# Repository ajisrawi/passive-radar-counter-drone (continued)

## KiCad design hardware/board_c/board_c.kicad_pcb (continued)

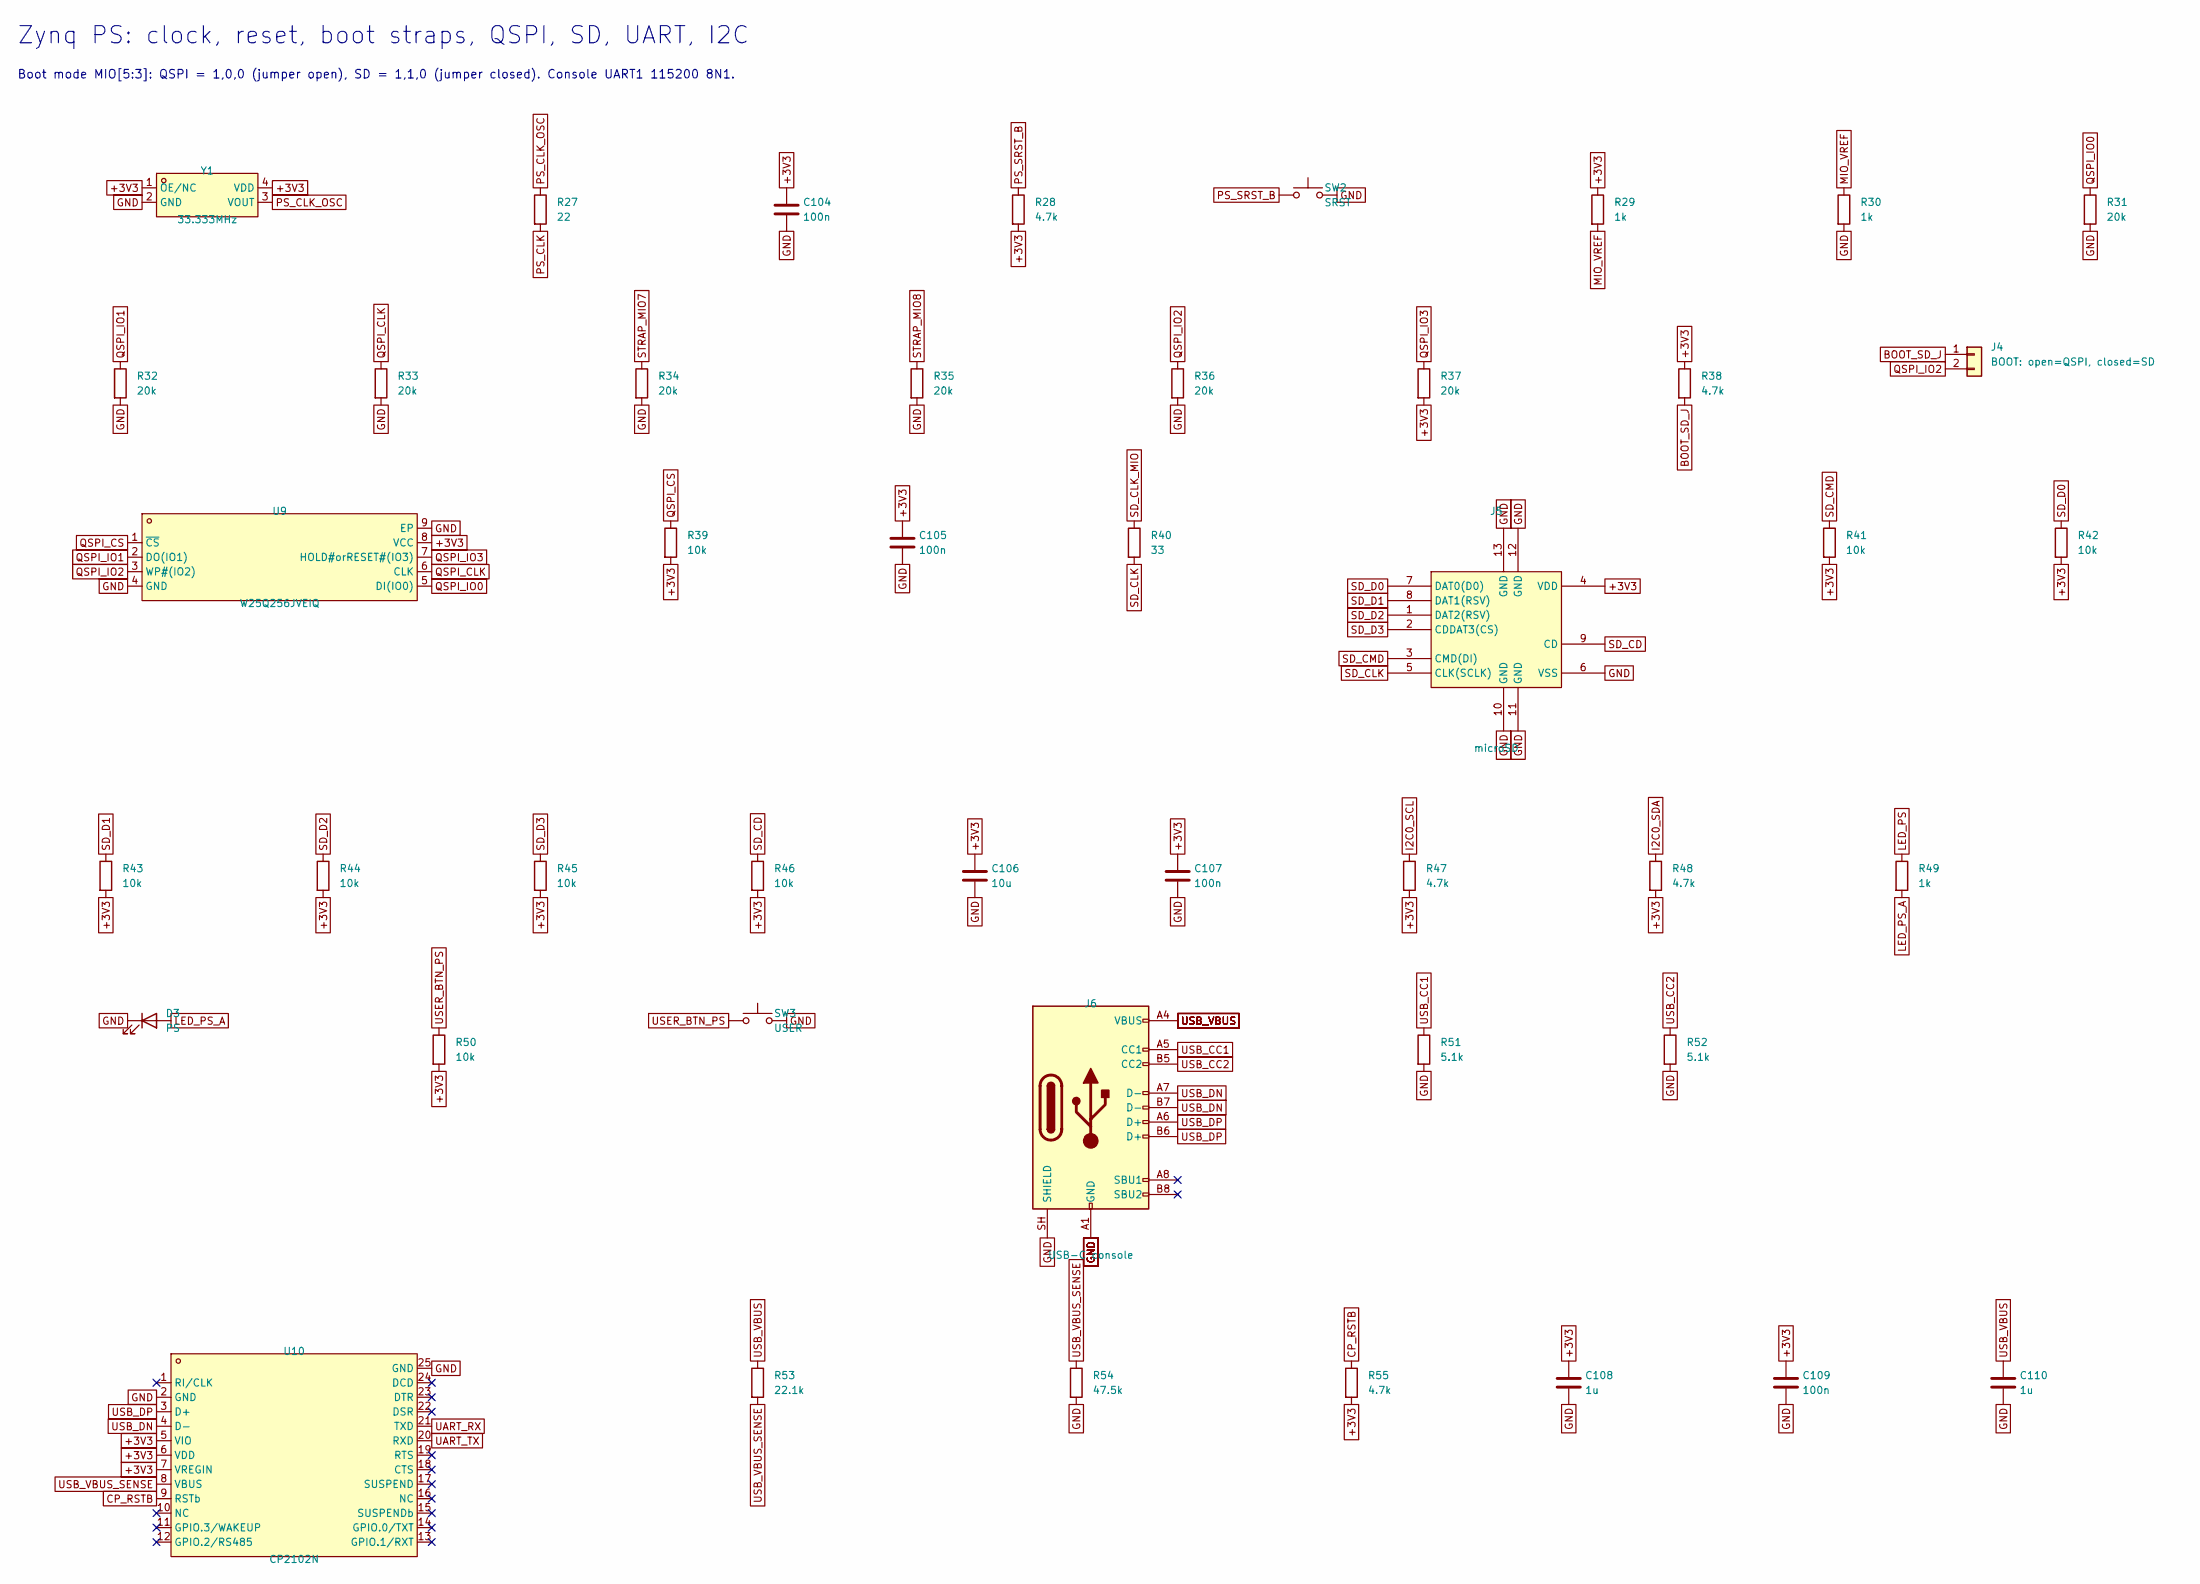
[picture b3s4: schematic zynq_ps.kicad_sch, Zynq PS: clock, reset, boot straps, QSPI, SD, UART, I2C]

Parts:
C104, C105, C107, C109: 100n; C_0402_1005Metric; LCSC C1525
C106: 10u; C_0603_1608Metric; LCSC C19702
C108, C110: 1u; C_0402_1005Metric; LCSC C52923
D3: PS; LED_0603_1608Metric
J4: BOOT: open=QSPI, closed=SD; PinHeader_1x02_P2.54mm_Vertical
J5: microSD; TF-SMD_TF-01A; MPN TF-01A; LCSC C91145
J6: USB-C console; USB_C_Receptacle_HRO_TYPE-C-31-M-12; LCSC C165948
R27: 22; R_0402_1005Metric
R28, R38, R47, R48, R55: 4.7k; R_0402_1005Metric; LCSC C25900
R29, R30, R49: 1k; R_0402_1005Metric; LCSC C11702
R31, R32, R33, R34, R35, R36, R37: 20k; R_0402_1005Metric
R39, R41, R42, R43, R44, R45, R46, R50: 10k; R_0402_1005Metric; LCSC C25744
R40: 33; R_0402_1005Metric
R51, R52: 5.1k; R_0402_1005Metric; LCSC C25905
R53: 22.1k; R_0402_1005Metric
R54: 47.5k; R_0402_1005Metric
SW2: SRST; SW_SPST_TL3342
SW3: USER; SW_SPST_TL3342
U9: W25Q256JVEIQ; WSON-8_L8.0-W6.10-P1.27-BL-EP; MPN W25Q256JVEIQ; LCSC C97522
U10: CP2102N; QFN-24_L4.0-W4.0-P0.50-TL-EP2.6; MPN CP2102N-A02-GQFN24R; LCSC C969151
Y1: 33.333MHz; OSC-SMD_4P-L5.0-W3.2-BL_OG8EL89CEI; MPN OG1EL89CEI-112YLC-33.333M; LCSC C5346412

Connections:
+3V3: C104.1, C105.1, C106.1, C107.1, C108.1, C109.1, J5.4 (VDD), R28.2, R29.1, R37.2, R38.1, R39.2, R41.2, R42.2, R43.2, R44.2, R45.2, R46.2, R47.2, R48.2, R50.2, R55.2, U9.8 (VCC), U10.5 (VIO), U10.6 (VDD), U10.7 (VREGIN), Y1.1 (OE/NC), Y1.4 (VDD); also elsewhere on the board
BOOT_SD_J: J4.1, R38.2
CP_RSTB: R55.1, U10.9 (RSTb)
GND: C104.2, C105.2, C106.2, C107.2, C108.2, C109.2, C110.2, D3.1 (K), J5.6 (VSS), J5.10 (GND), J5.11 (GND), J5.12 (GND), J5.13 (GND), J6.A1 (GND), J6.A12 (GND), J6.B1 (GND), J6.B12 (GND), J6.SH (SHIELD), R30.2, R31.2, R32.2, R33.2, R34.2, R35.2, R36.2, R51.2, R52.2, R54.2, SW2.2, SW3.2, U9.4 (GND), U9.9 (EP), U10.2 (GND), U10.25 (GND), Y1.2 (GND); also elsewhere on the board
I2C0_SCL: R47.1; also elsewhere on the board
I2C0_SDA: R48.1; also elsewhere on the board
LED_PS: R49.1; also elsewhere on the board
LED_PS_A: D3.2 (A), R49.2
MIO_VREF: R29.2, R30.1; also elsewhere on the board
PS_CLK: R27.2; also elsewhere on the board
PS_CLK_OSC: R27.1, Y1.3 (VOUT)
PS_SRST_B: R28.1, SW2.1; also elsewhere on the board
QSPI_CLK: R33.1, U9.6 (CLK); also elsewhere on the board
QSPI_CS: R39.1, U9.1 (~CS); also elsewhere on the board
QSPI_IO0: R31.1, U9.5 (DI(IO0)); also elsewhere on the board
QSPI_IO1: R32.1, U9.2 (DO(IO1)); also elsewhere on the board
QSPI_IO2: J4.2, R36.1, U9.3 (WP#(IO2)); also elsewhere on the board
QSPI_IO3: R37.1, U9.7 (HOLD#orRESET#(IO3)); also elsewhere on the board
SD_CD: J5.9 (CD), R46.1; also elsewhere on the board
SD_CLK: J5.5 (CLK(SCLK)), R40.2
SD_CLK_MIO: R40.1; also elsewhere on the board
SD_CMD: J5.3 (CMD(DI)), R41.1; also elsewhere on the board
SD_D0: J5.7 (DAT0(D0)), R42.1; also elsewhere on the board
SD_D1: J5.8 (DAT1(RSV)), R43.1; also elsewhere on the board
SD_D2: J5.1 (DAT2(RSV)), R44.1; also elsewhere on the board
SD_D3: J5.2 (CDDAT3(CS)), R45.1; also elsewhere on the board
STRAP_MIO7: R34.1; also elsewhere on the board
STRAP_MIO8: R35.1; also elsewhere on the board
UART_RX: U10.21 (TXD); also elsewhere on the board
UART_TX: U10.20 (RXD); also elsewhere on the board
USB_CC1: J6.A5 (CC1), R51.1
USB_CC2: J6.B5 (CC2), R52.1
USB_DN: J6.A7 (D-), J6.B7 (D-), U10.4 (D-)
USB_DP: J6.A6 (D+), J6.B6 (D+), U10.3 (D+)
USB_VBUS: C110.1, J6.A4 (VBUS), J6.A9 (VBUS), J6.B4 (VBUS), J6.B9 (VBUS), R53.1
USB_VBUS_SENSE: R53.2, R54.1, U10.8 (VBUS)
USER_BTN_PS: R50.1, SW3.1; also elsewhere on the board

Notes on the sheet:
Zynq PS: clock, reset, boot straps, QSPI, SD, UART, I2C
Boot mode MIO[5:3]: QSPI = 1,0,0 (jumper open), SD = 1,1,0 (jumper closed). Console UART1 115200 8N1.

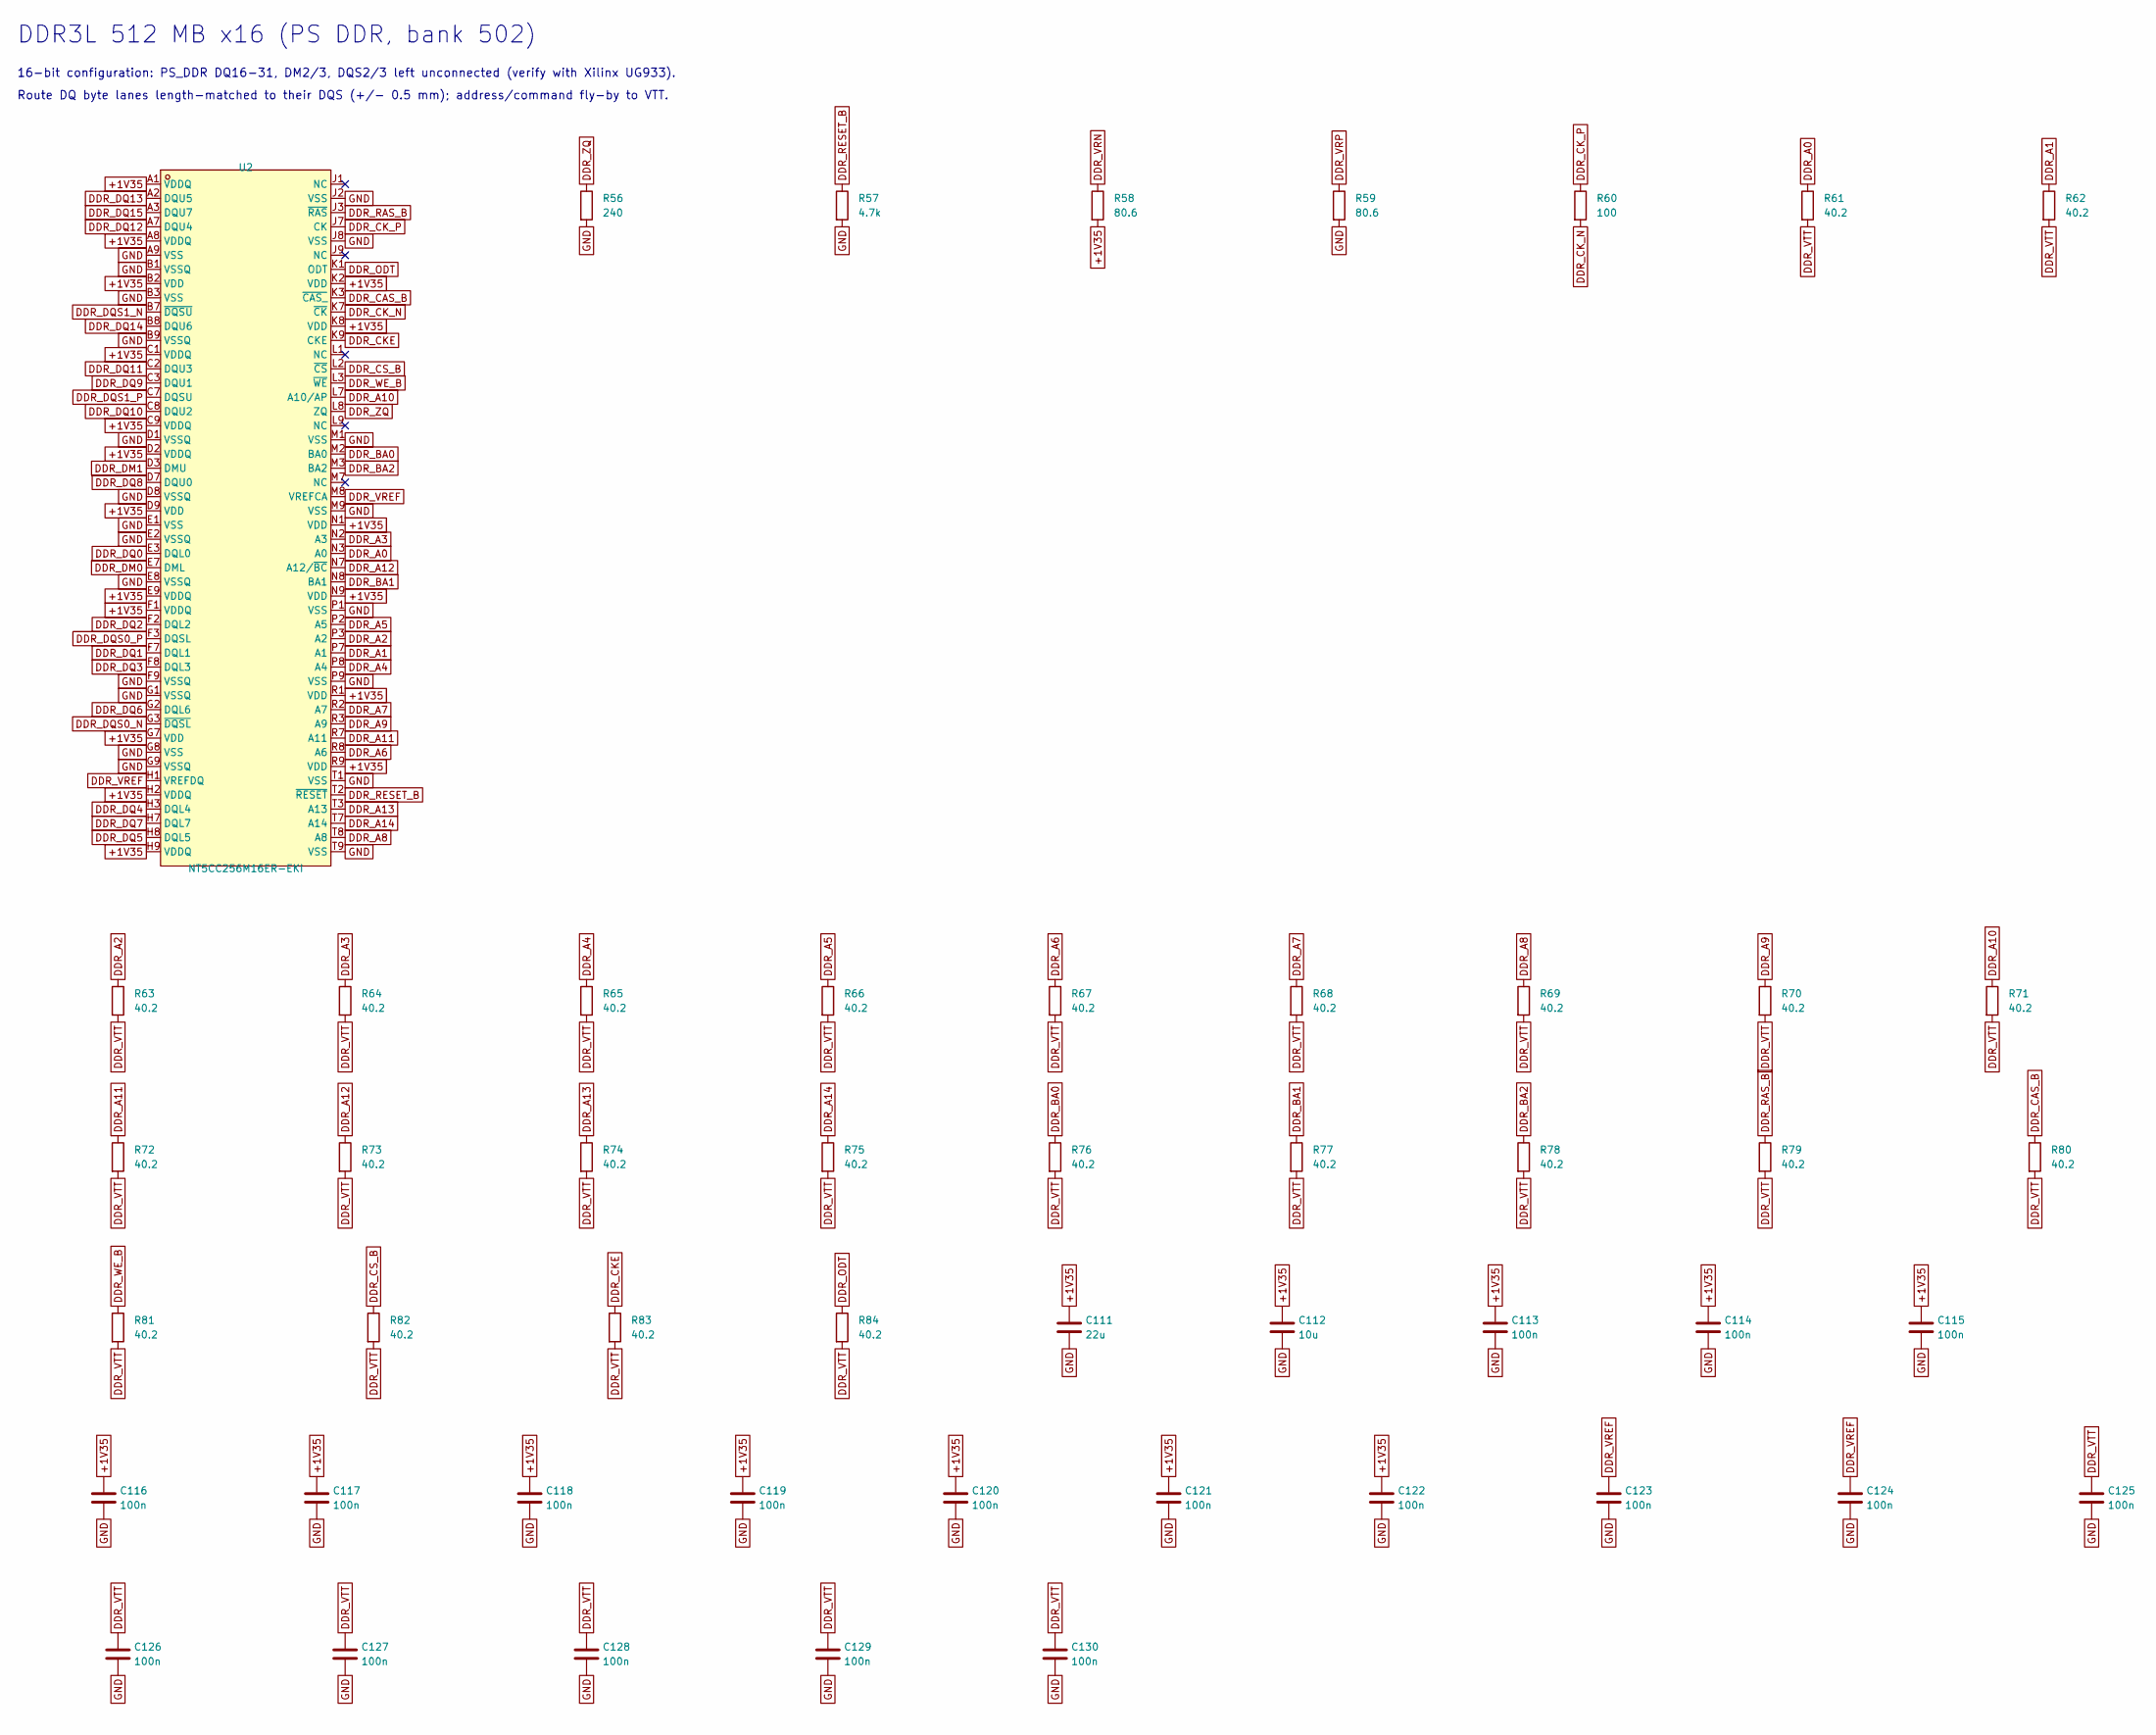
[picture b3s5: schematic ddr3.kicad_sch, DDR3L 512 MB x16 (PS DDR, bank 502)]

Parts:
C111: 22u; C_0805_2012Metric; LCSC C45783
C112: 10u; C_0603_1608Metric; LCSC C19702
C113, C114, C115, C116, C117, C118, C119, C120, C121, C122, C123, C124, C125, C126, C127, C128, C129, C130: 100n; C_0402_1005Metric; LCSC C1525
R56: 240; R_0402_1005Metric; Tolerance 1%
R57: 4.7k; R_0402_1005Metric; LCSC C25900
R58, R59: 80.6; R_0402_1005Metric; Tolerance 1%
R60: 100; R_0402_1005Metric
R61, R62, R63, R64, R65, R66, R67, R68, R69, R70, R71, R72, R73, R74, R75, R76, R77, R78, R79, R80, R81, R82, R83, R84: 40.2; R_0402_1005Metric
U2: NT5CC256M16ER-EKI; TFBGA-96_L13.0-W8.0-R16-C6-P0.80-TL; MPN NT5CC256M16ER-EKI; LCSC C2841153

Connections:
+1V35: C111.1, C112.1, C113.1, C114.1, C115.1, C116.1, C117.1, C118.1, C119.1, C120.1, C121.1, C122.1, R58.2, U2.A1 (VDDQ), U2.A8 (VDDQ), U2.B2 (VDD), U2.C1 (VDDQ), U2.C9 (VDDQ), U2.D2 (VDDQ), U2.D9 (VDD), U2.E9 (VDDQ), U2.F1 (VDDQ), U2.G7 (VDD), U2.H2 (VDDQ), U2.H9 (VDDQ), U2.K2 (VDD), U2.K8 (VDD), U2.N1 (VDD), U2.N9 (VDD), U2.R1 (VDD), U2.R9 (VDD); also elsewhere on the board
DDR_A0: R61.1, U2.N3 (A0); also elsewhere on the board
DDR_A1: R62.1, U2.P7 (A1); also elsewhere on the board
DDR_A2: R63.1, U2.P3 (A2); also elsewhere on the board
DDR_A3: R64.1, U2.N2 (A3); also elsewhere on the board
DDR_A4: R65.1, U2.P8 (A4); also elsewhere on the board
DDR_A5: R66.1, U2.P2 (A5); also elsewhere on the board
DDR_A6: R67.1, U2.R8 (A6); also elsewhere on the board
DDR_A7: R68.1, U2.R2 (A7); also elsewhere on the board
DDR_A8: R69.1, U2.T8 (A8); also elsewhere on the board
DDR_A9: R70.1, U2.R3 (A9); also elsewhere on the board
DDR_A10: R71.1, U2.L7 (A10/AP); also elsewhere on the board
DDR_A11: R72.1, U2.R7 (A11); also elsewhere on the board
DDR_A12: R73.1, U2.N7 (A12/~BC); also elsewhere on the board
DDR_A13: R74.1, U2.T3 (A13); also elsewhere on the board
DDR_A14: R75.1, U2.T7 (A14); also elsewhere on the board
DDR_BA0: R76.1, U2.M2 (BA0); also elsewhere on the board
DDR_BA1: R77.1, U2.N8 (BA1); also elsewhere on the board
DDR_BA2: R78.1, U2.M3 (BA2); also elsewhere on the board
DDR_CAS_B: R80.1, U2.K3 (~CAS_); also elsewhere on the board
DDR_CKE: R83.1, U2.K9 (CKE); also elsewhere on the board
DDR_CK_N: R60.2, U2.K7 (~CK); also elsewhere on the board
DDR_CK_P: R60.1, U2.J7 (CK); also elsewhere on the board
DDR_CS_B: R82.1, U2.L2 (~CS); also elsewhere on the board
DDR_DM0: U2.E7 (DML); also elsewhere on the board
DDR_DM1: U2.D3 (DMU); also elsewhere on the board
DDR_DQ0: U2.E3 (DQL0); also elsewhere on the board
DDR_DQ1: U2.F7 (DQL1); also elsewhere on the board
DDR_DQ2: U2.F2 (DQL2); also elsewhere on the board
DDR_DQ3: U2.F8 (DQL3); also elsewhere on the board
DDR_DQ4: U2.H3 (DQL4); also elsewhere on the board
DDR_DQ5: U2.H8 (DQL5); also elsewhere on the board
DDR_DQ6: U2.G2 (DQL6); also elsewhere on the board
DDR_DQ7: U2.H7 (DQL7); also elsewhere on the board
DDR_DQ8: U2.D7 (DQU0); also elsewhere on the board
DDR_DQ9: U2.C3 (DQU1); also elsewhere on the board
DDR_DQ10: U2.C8 (DQU2); also elsewhere on the board
DDR_DQ11: U2.C2 (DQU3); also elsewhere on the board
DDR_DQ12: U2.A7 (DQU4); also elsewhere on the board
DDR_DQ13: U2.A2 (DQU5); also elsewhere on the board
DDR_DQ14: U2.B8 (DQU6); also elsewhere on the board
DDR_DQ15: U2.A3 (DQU7); also elsewhere on the board
DDR_DQS0_N: U2.G3 (~DQSL); also elsewhere on the board
DDR_DQS0_P: U2.F3 (DQSL); also elsewhere on the board
DDR_DQS1_N: U2.B7 (~DQSU); also elsewhere on the board
DDR_DQS1_P: U2.C7 (DQSU); also elsewhere on the board
DDR_ODT: R84.1, U2.K1 (ODT); also elsewhere on the board
DDR_RAS_B: R79.1, U2.J3 (~RAS); also elsewhere on the board
DDR_RESET_B: R57.1, U2.T2 (~RESET); also elsewhere on the board
DDR_VREF: C123.1, C124.1, U2.H1 (VREFDQ), U2.M8 (VREFCA); also elsewhere on the board
DDR_VRN: R58.1; also elsewhere on the board
DDR_VRP: R59.1; also elsewhere on the board
DDR_VTT: C125.1, C126.1, C127.1, C128.1, C129.1, C130.1, R61.2, R62.2, R63.2, R64.2, R65.2, R66.2, R67.2, R68.2, R69.2, R70.2, R71.2, R72.2, R73.2, R74.2, R75.2, R76.2, R77.2, R78.2, R79.2, R80.2, R81.2, R82.2, R83.2, R84.2; also elsewhere on the board
DDR_WE_B: R81.1, U2.L3 (~WE); also elsewhere on the board
DDR_ZQ: R56.1, U2.L8 (ZQ)
GND: C111.2, C112.2, C113.2, C114.2, C115.2, C116.2, C117.2, C118.2, C119.2, C120.2, C121.2, C122.2, C123.2, C124.2, C125.2, C126.2, C127.2, C128.2, C129.2, C130.2, R56.2, R57.2, R59.2, U2.A9 (VSS), U2.B1 (VSSQ), U2.B3 (VSS), U2.B9 (VSSQ), U2.D1 (VSSQ), U2.D8 (VSSQ), U2.E1 (VSS), U2.E2 (VSSQ), U2.E8 (VSSQ), U2.F9 (VSSQ), U2.G1 (VSSQ), U2.G8 (VSS), U2.G9 (VSSQ), U2.J2 (VSS), U2.J8 (VSS), U2.M1 (VSS), U2.M9 (VSS), U2.P1 (VSS), U2.P9 (VSS), U2.T1 (VSS), U2.T9 (VSS); also elsewhere on the board

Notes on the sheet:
DDR3L 512 MB x16 (PS DDR, bank 502)
16-bit configuration: PS_DDR DQ16-31, DM2/3, DQS2/3 left unconnected (verify with Xilinx UG933).
Route DQ byte lanes length-matched to their DQS (+/- 0.5 mm); address/command fly-by to VTT.

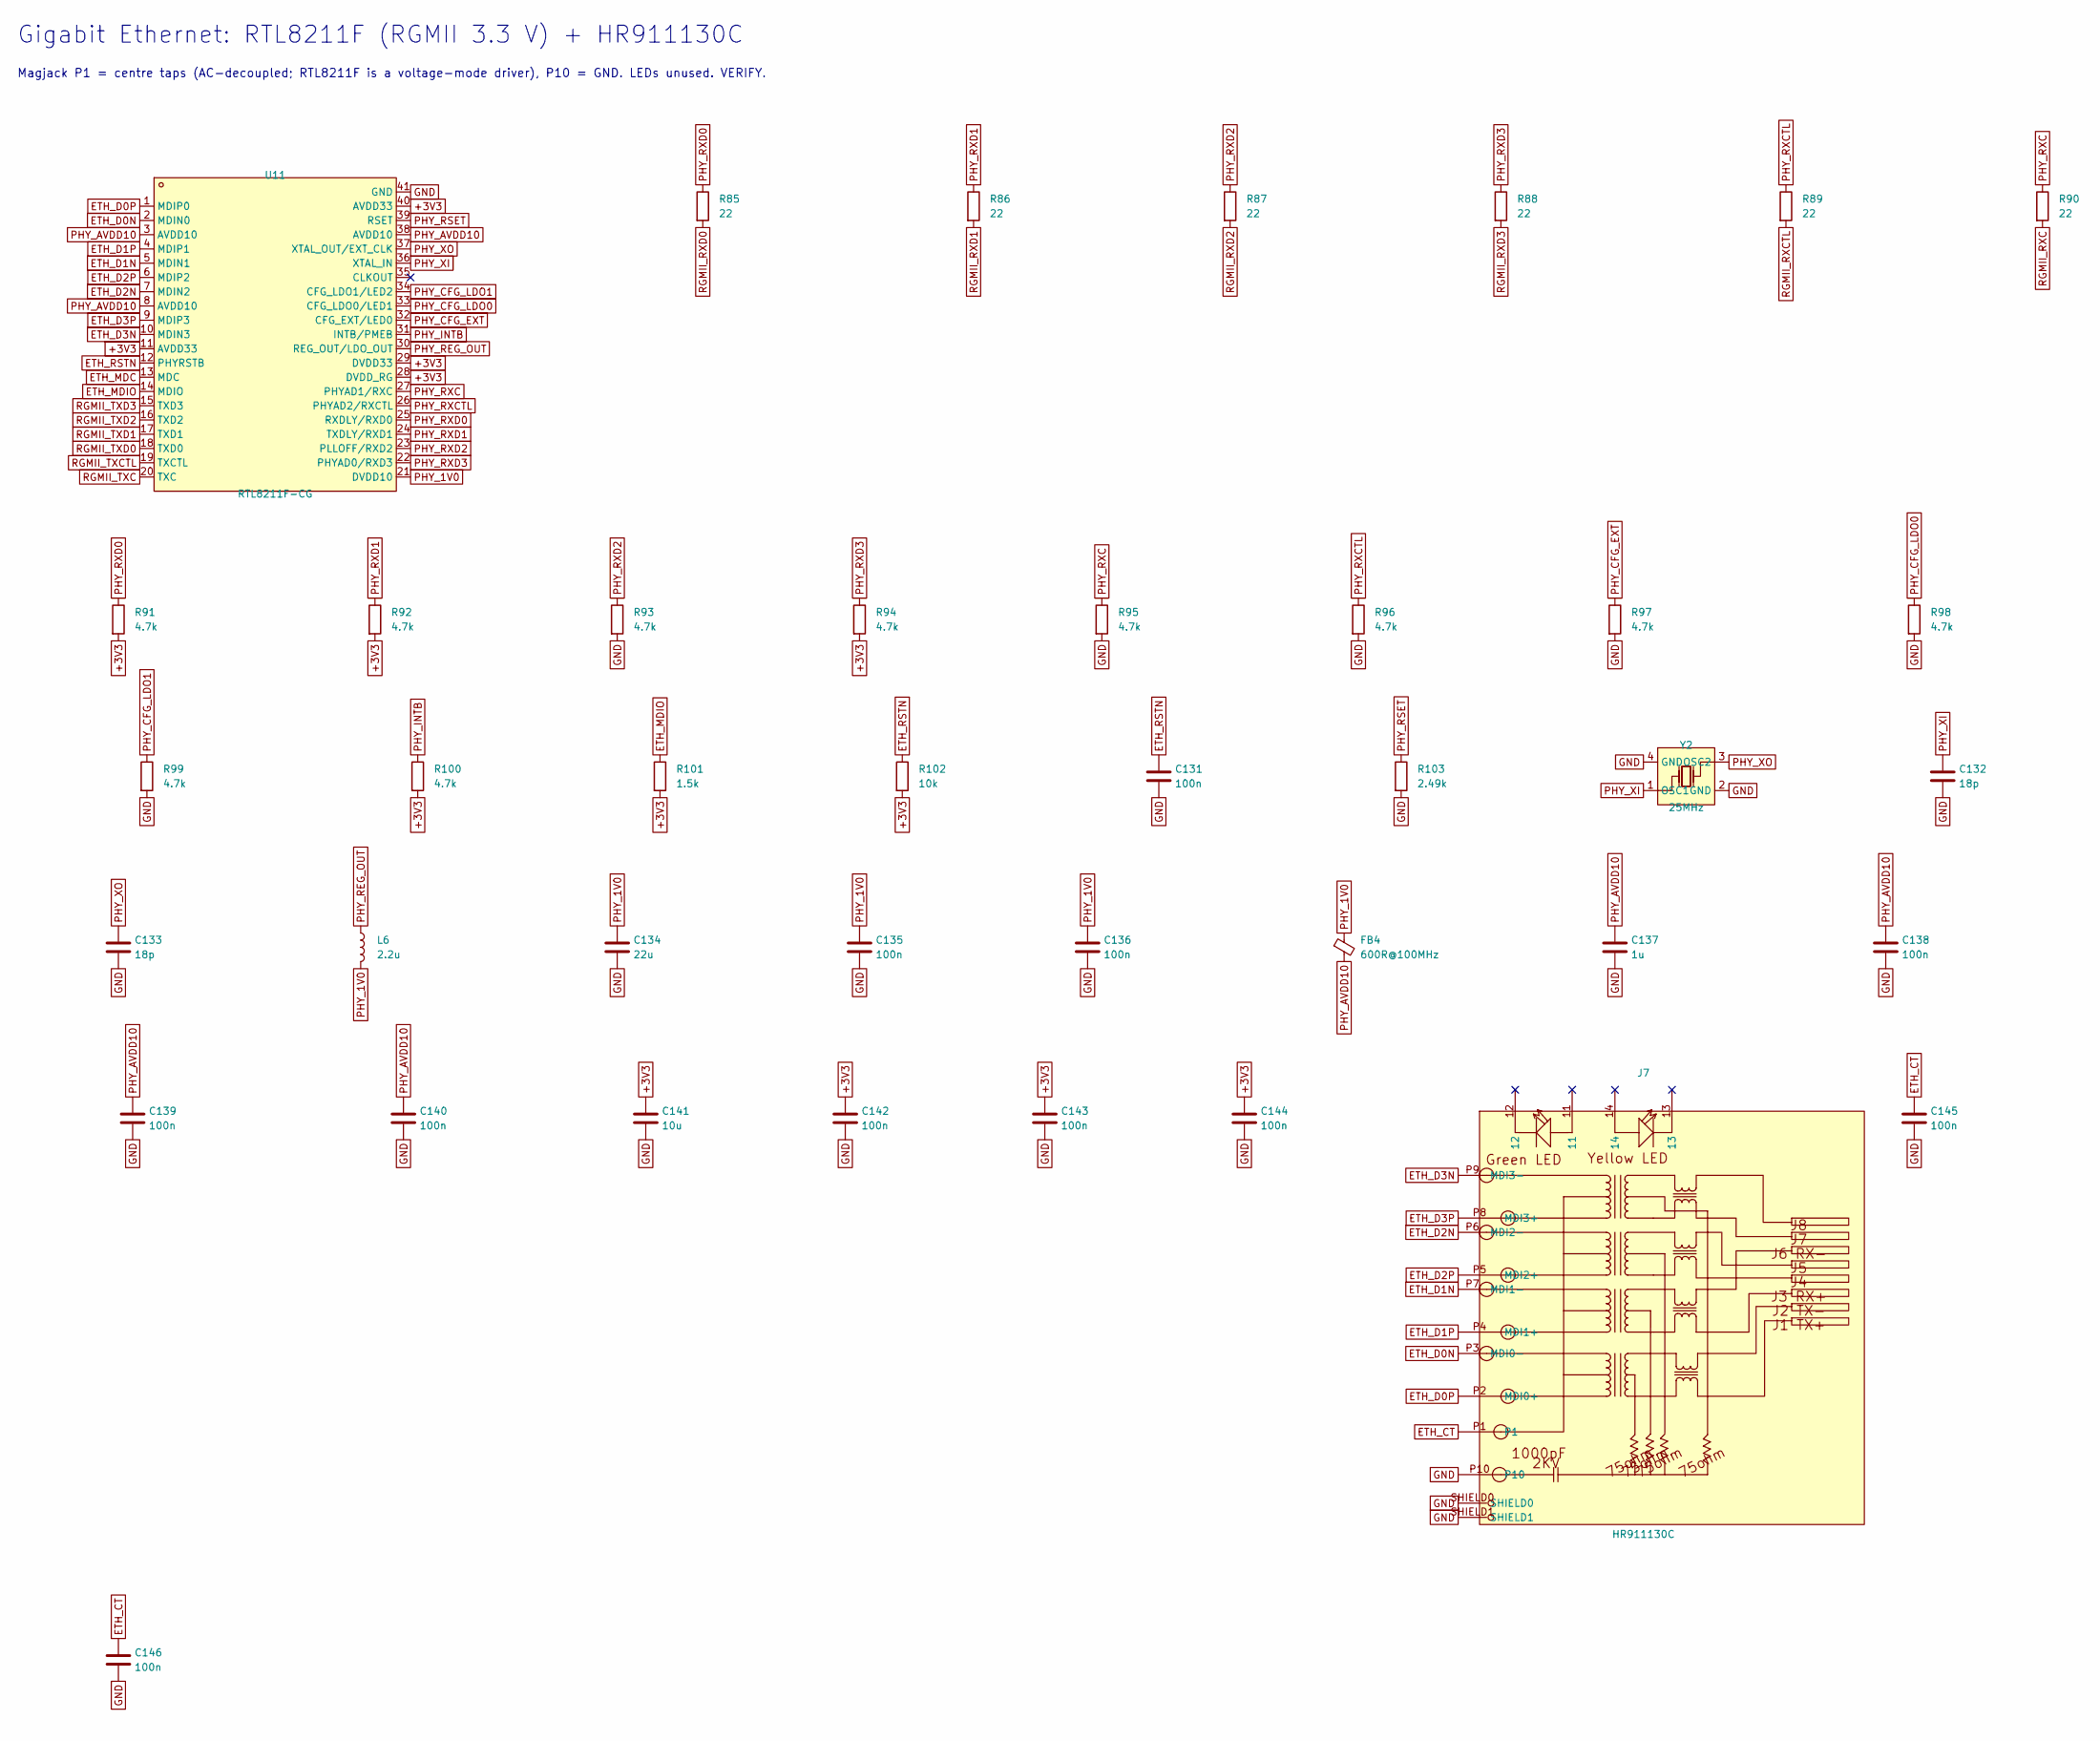
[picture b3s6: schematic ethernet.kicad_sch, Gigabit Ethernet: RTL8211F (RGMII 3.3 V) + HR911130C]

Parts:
C131, C135, C136, C138, C139, C140, C142, C143, C144, C145, C146: 100n; C_0402_1005Metric; LCSC C1525
C132, C133: 18p; C_0402_1005Metric
C134: 22u; C_0805_2012Metric; LCSC C45783
C137: 1u; C_0402_1005Metric; LCSC C52923
C141: 10u; C_0603_1608Metric; LCSC C19702
FB4: 600R@100MHz; L_0603_1608Metric
J7: HR911130C; RJ45-TH_HR911130C; MPN HR911130C; LCSC C50933
L6: 2.2u; L_0603_1608Metric
R85, R86, R87, R88, R89, R90: 22; R_0402_1005Metric
R91, R92, R93, R94, R95, R96, R97, R98, R99, R100: 4.7k; R_0402_1005Metric; LCSC C25900
R101: 1.5k; R_0402_1005Metric
R102: 10k; R_0402_1005Metric; LCSC C25744
R103: 2.49k; R_0402_1005Metric; Tolerance 1%
U11: RTL8211F-CG; WQFN-40_L5.0-W5.0-P0.4-BL-EP; MPN RTL8211F-CG; LCSC C187932
Y2: 25MHz; CRYSTAL-SMD_4P-L3.2-W2.5-BL; MPN X322525MOB4SI; LCSC C9006

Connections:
+3V3: C141.1, C142.1, C143.1, C144.1, R91.2, R92.2, R94.2, R100.2, R101.2, R102.2, U11.11 (AVDD33), U11.28 (DVDD_RG), U11.29 (DVDD33), U11.40 (AVDD33); also elsewhere on the board
ETH_CT: C145.1, C146.1, J7.P1
ETH_D0N: J7.P3 (MDI0-), U11.2 (MDIN0)
ETH_D0P: J7.P2 (MDI0+), U11.1 (MDIP0)
ETH_D1N: J7.P7 (MDI1-), U11.5 (MDIN1)
ETH_D1P: J7.P4 (MDI1+), U11.4 (MDIP1)
ETH_D2N: J7.P6 (MDI2-), U11.7 (MDIN2)
ETH_D2P: J7.P5 (MDI2+), U11.6 (MDIP2)
ETH_D3N: J7.P9 (MDI3-), U11.10 (MDIN3)
ETH_D3P: J7.P8 (MDI3+), U11.9 (MDIP3)
ETH_MDC: U11.13 (MDC); also elsewhere on the board
ETH_MDIO: R101.1, U11.14 (MDIO); also elsewhere on the board
ETH_RSTN: C131.1, R102.1, U11.12 (PHYRSTB); also elsewhere on the board
GND: C131.2, C132.2, C133.2, C134.2, C135.2, C136.2, C137.2, C138.2, C139.2, C140.2, C141.2, C142.2, C143.2, C144.2, C145.2, C146.2, J7.P10, J7.SHIELD0, J7.SHIELD1, R93.2, R95.2, R96.2, R97.2, R98.2, R99.2, R103.2, U11.41 (GND), Y2.2 (GND), Y2.4 (GND); also elsewhere on the board
PHY_1V0: C134.1, C135.1, C136.1, FB4.1, L6.2, U11.21 (DVDD10)
PHY_AVDD10: C137.1, C138.1, C139.1, C140.1, FB4.2, U11.3 (AVDD10), U11.8 (AVDD10), U11.38 (AVDD10)
PHY_CFG_EXT: R97.1, U11.32 (CFG_EXT/LED0)
PHY_CFG_LDO0: R98.1, U11.33 (CFG_LDO0/LED1)
PHY_CFG_LDO1: R99.1, U11.34 (CFG_LDO1/LED2)
PHY_INTB: R100.1, U11.31 (INTB/PMEB)
PHY_REG_OUT: L6.1, U11.30 (REG_OUT/LDO_OUT)
PHY_RSET: R103.1, U11.39 (RSET)
PHY_RXC: R90.1, R95.1, U11.27 (PHYAD1/RXC)
PHY_RXCTL: R89.1, R96.1, U11.26 (PHYAD2/RXCTL)
PHY_RXD0: R85.1, R91.1, U11.25 (RXDLY/RXD0)
PHY_RXD1: R86.1, R92.1, U11.24 (TXDLY/RXD1)
PHY_RXD2: R87.1, R93.1, U11.23 (PLLOFF/RXD2)
PHY_RXD3: R88.1, R94.1, U11.22 (PHYAD0/RXD3)
PHY_XI: C132.1, U11.36 (XTAL_IN), Y2.1 (OSC1)
PHY_XO: C133.1, U11.37 (XTAL_OUT/EXT_CLK), Y2.3 (OSC2)
RGMII_RXC: R90.2; also elsewhere on the board
RGMII_RXCTL: R89.2; also elsewhere on the board
RGMII_RXD0: R85.2; also elsewhere on the board
RGMII_RXD1: R86.2; also elsewhere on the board
RGMII_RXD2: R87.2; also elsewhere on the board
RGMII_RXD3: R88.2; also elsewhere on the board
RGMII_TXC: U11.20 (TXC); also elsewhere on the board
RGMII_TXCTL: U11.19 (TXCTL); also elsewhere on the board
RGMII_TXD0: U11.18 (TXD0); also elsewhere on the board
RGMII_TXD1: U11.17 (TXD1); also elsewhere on the board
RGMII_TXD2: U11.16 (TXD2); also elsewhere on the board
RGMII_TXD3: U11.15 (TXD3); also elsewhere on the board

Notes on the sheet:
Gigabit Ethernet: RTL8211F (RGMII 3.3 V) + HR911130C
Magjack P1 = centre taps (AC-decoupled; RTL8211F is a voltage-mode driver), P10 = GND. LEDs unused. VERIFY.

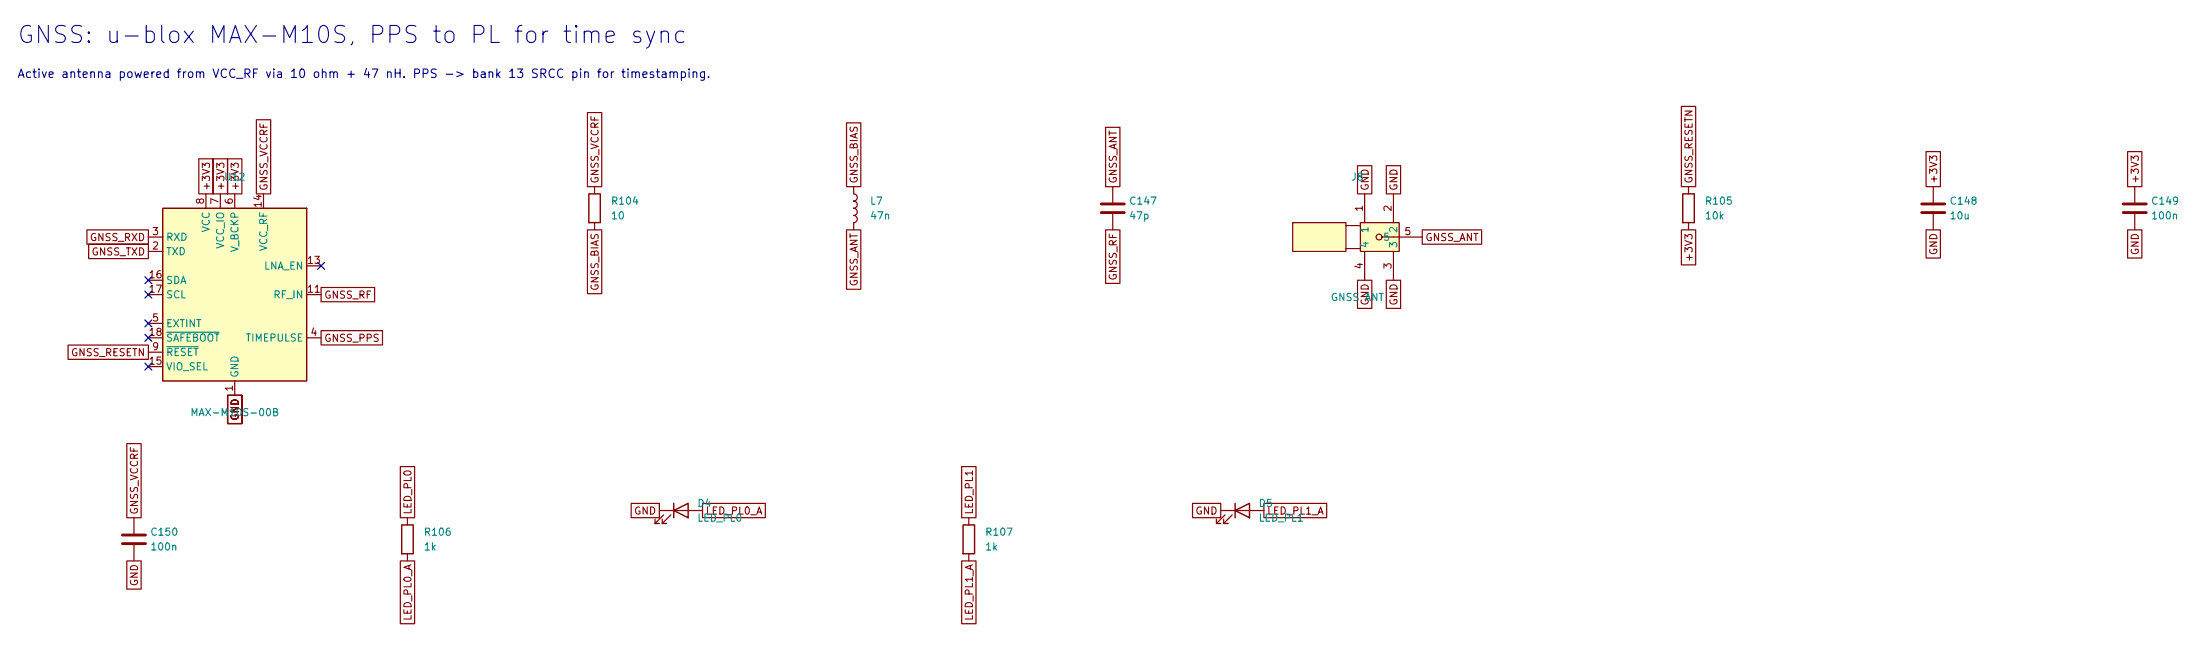
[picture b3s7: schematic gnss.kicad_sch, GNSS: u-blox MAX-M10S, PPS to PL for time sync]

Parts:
C147: 47p; C_0402_1005Metric
C148: 10u; C_0603_1608Metric; LCSC C19702
C149, C150: 100n; C_0402_1005Metric; LCSC C1525
D4: LED_PL0; LED_0603_1608Metric
D5: LED_PL1; LED_0603_1608Metric
J8: GNSS ANT; SMA-TH_BWSMA-KE-Z001; MPN BWSMA-KE-Z001; LCSC C496549
L7: 47n; L_0402_1005Metric
R104: 10; R_0402_1005Metric
R105: 10k; R_0402_1005Metric; LCSC C25744
R106, R107: 1k; R_0402_1005Metric; LCSC C11702
U12: MAX-M10S-00B; ublox_MAX; LCSC C4153167

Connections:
+3V3: C148.1, C149.1, R105.2, U12.6 (V_BCKP), U12.7 (VCC_IO), U12.8 (VCC); also elsewhere on the board
GND: C148.2, C149.2, C150.2, D4.1 (K), D5.1 (K), J8.1, J8.2, J8.3, J8.4, U12.1 (GND), U12.10 (GND), U12.12 (GND); also elsewhere on the board
GNSS_ANT: C147.1, J8.5, L7.2
GNSS_BIAS: L7.1, R104.2
GNSS_PPS: U12.4 (TIMEPULSE); also elsewhere on the board
GNSS_RESETN: R105.1, U12.9 (~RESET); also elsewhere on the board
GNSS_RF: C147.2, U12.11 (RF_IN)
GNSS_RXD: U12.3 (RXD); also elsewhere on the board
GNSS_TXD: U12.2 (TXD); also elsewhere on the board
GNSS_VCCRF: C150.1, R104.1, U12.14 (VCC_RF)
LED_PL0: R106.1; also elsewhere on the board
LED_PL0_A: D4.2 (A), R106.2
LED_PL1: R107.1; also elsewhere on the board
LED_PL1_A: D5.2 (A), R107.2

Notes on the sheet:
GNSS: u-blox MAX-M10S, PPS to PL for time sync
Active antenna powered from VCC_RF via 10 ohm + 47 nH. PPS -> bank 13 SRCC pin for timestamping.
